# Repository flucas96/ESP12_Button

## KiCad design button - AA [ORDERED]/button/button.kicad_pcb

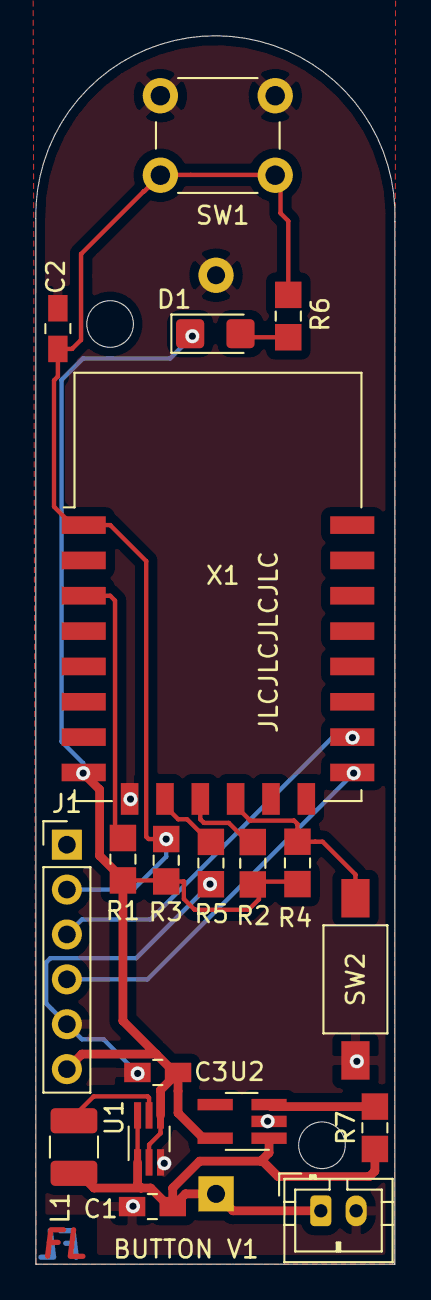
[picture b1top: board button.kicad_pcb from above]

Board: 2 copper layers, 20.3 x 69.5 mm, 20 parts (1 on the bottom side), 13 nets.

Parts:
BT1: Battery_Cell; BatteryHolder_Keystone_2460_1xAA
BT2: Battery_Cell; JST_PH_B2B-PH-K_1x02_P2.00mm_Vertical
C1, C3: 10uF; C_0805_2012handsodermod
C2: 100nF; C_0805_2012handsodermod
D1: LED; LED_1206_3216Metric_Castellated
J1: Conn_01x06_Male; PinHeader_1x06_P2.54mm_Vertical
L1: 4.7 uH; L_1210_3225Metric_Pad1.42x2.65mm_HandSolder
R1, R2, R3, R4, R7: 10k; R_0805_2012handsoldermod
R5: 4.7k; R_0805_2012handsoldermod
R6: 1k; R_0805_2012handsoldermod
SW1: SW_Push; SW_PUSH_6mm
SW2: SW_Push; button_smd_hmsensor
U1: TLV61224; SOT-363_SC-70-6_Handsoldering
U2: AP2112K-3.3; SOT-23-5_HandSolderingmod
X1: ESP-12E

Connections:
/EN: R1.2, X1.3
/GND: BT1.2, BT2.2, C1.1, C2.1, C3.2, J1.5, R5.1, SW1.2, SW2.2, U1.3, U2.2, X1.9
/GPIO0: R4.2, SW2.1, X1.12
/GPIO2: R2.2, X1.11
/GPIO15: R5.2, X1.10
/RST: C2.2, J1.2, R3.2, R6.2, SW1.1, X1.1
/RX: J1.4, X1.15
/TX: J1.3, X1.16
/VCC: C3.1, D1.1, J1.6, R1.1, R2.1, R3.1, R4.1, U1.2, U1.4, U2.5, X1.8
unnamed: BT1.1, BT2.1, C1.2, L1.1, R7.1, U1.1, U1.6, U2.1
unnamed: D1.2, R6.1
unnamed: L1.2, U1.5
unnamed: R7.2, U2.3

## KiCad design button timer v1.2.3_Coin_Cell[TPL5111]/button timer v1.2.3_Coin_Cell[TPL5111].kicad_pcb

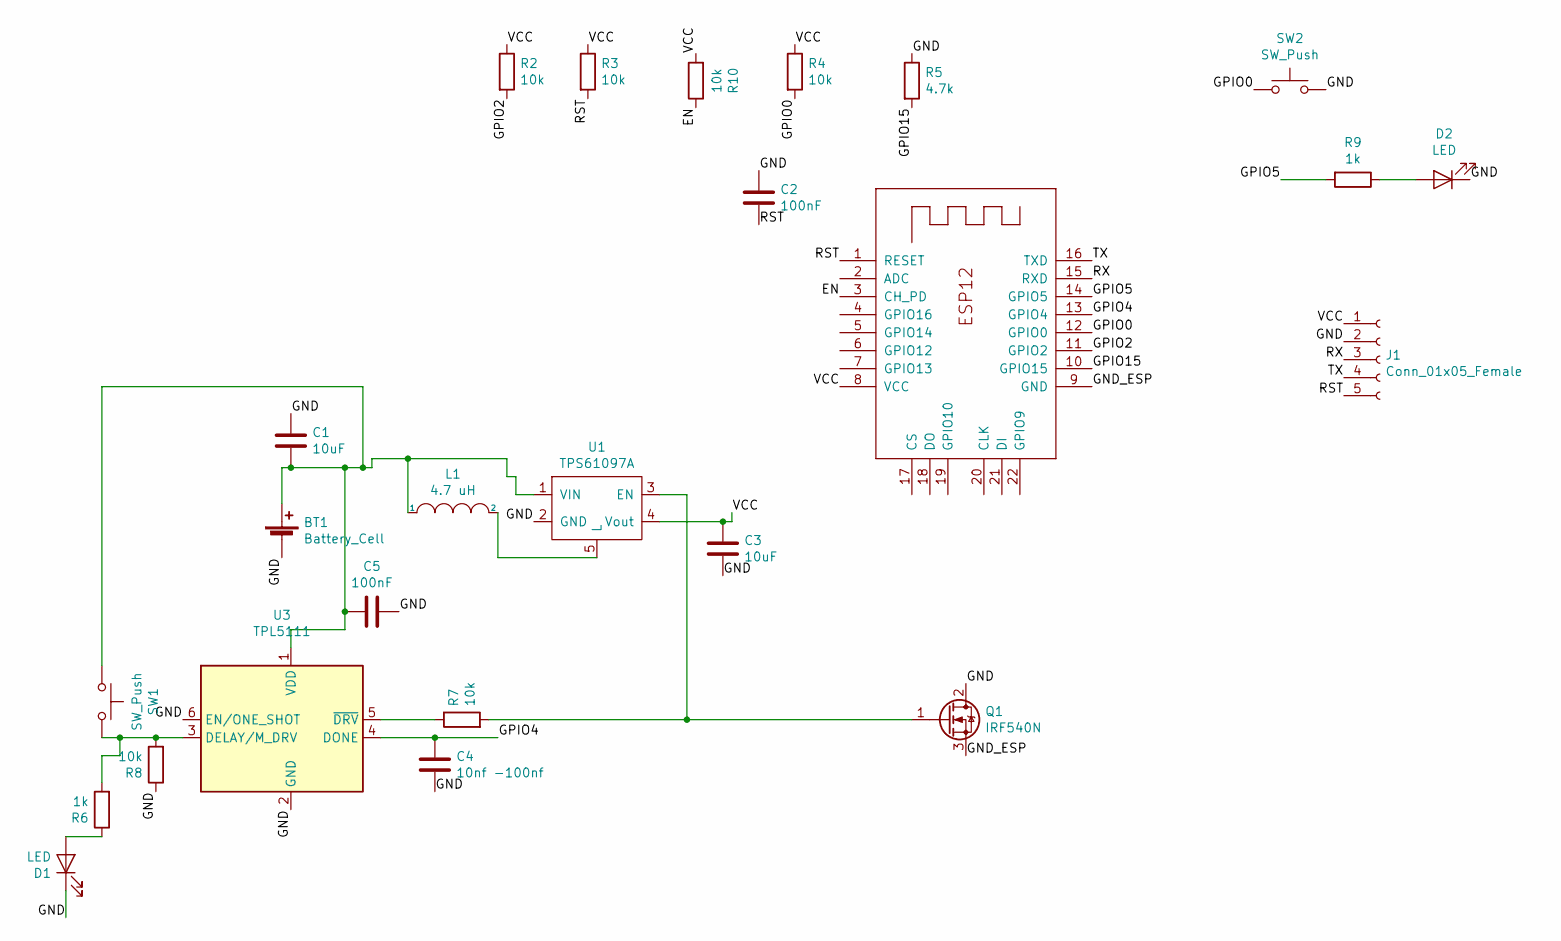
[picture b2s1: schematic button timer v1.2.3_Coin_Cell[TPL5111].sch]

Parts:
BT1: Battery_Cell; BatteryHolder_Keystone_1058_1x2032
C1, C3: 10uF; C_0805_2012handsodermod
C2, C5: 100nF; C_0805_2012handsodermod
C4: 10nf -100nf; C_0402_1005Metric_Pad0.74x0.62mm_HandSoldermod
D1: LED; LED_1206_3216Metric_Castellated
D2: LED; LED_0805_2012Metric_Castellated
J1: Conn_01x05_Female; PinSocket_1x05_P2.54mm_Vertical_mod
L1: 4.7 uH; SMD-1210_Pol_inductor
Q1: IRF540N; SOT-23
R2, R3, R4, R7, R8: 10k; R_0805_2012handsoldermod
R5: 4.7k; R_0805_2012handsoldermod
R6, R9: 1k; R_0805_2012handsoldermod
R10: 10k; R_0603_1608Metric_Pad0.98x0.95mm_HandSolder
SW1: SW_Push; SW_PUSH_6mm_H8mm_mod
SW2: SW_Push; SW_SPST_B3U-1000P_mod
U1: TPS61097A; SOT-23-5_HandSolderingmod
U3: TPL5111; SOT-23-6handsoldering
X1: ESP-12E; ESP-12Elesssilk

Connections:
/EN: R10.1, X1.3 (CH_PD)
/GND: BT1.2 (-), C1.1, C2.1, C3.2, C4.2, C5.1, D1.1 (K), D2.1 (K), J1.2, Q1.2 (D), R5.1, R8.1, SW2.2, U1.2 (GND), U3.2 (GND), U3.6 (EN/ONE_SHOT)
/GND_ESP: Q1.3 (S), X1.9 (GND)
/GPIO0: R4.2, SW2.1, X1.12 (GPIO0)
/GPIO2: R2.2, X1.11 (GPIO2)
/GPIO4: C4.1, U3.4 (DONE), X1.13 (GPIO4)
/GPIO5: R9.2, X1.14 (GPIO5)
/GPIO15: R5.2, X1.10 (GPIO15)
/RST: C2.2, J1.5, R3.2, X1.1 (RESET)
/RX: J1.3, X1.15 (RXD)
/TX: J1.4, X1.16 (TXD)
/VCC: C3.1, J1.1, R2.1, R3.1, R4.1, R10.2, U1.4 (Vout), X1.8 (VCC)
unnamed: BT1.1 (+), C1.2, C5.2, L1.1, SW1.1, U1.1 (VIN), U3.1 (VDD)
unnamed: D1.2 (A), R6.1
unnamed: D2.2 (A), R9.1
unnamed: L1.2, U1.5 (L)
unnamed: Q1.1 (G), R7.2, U1.3 (EN)
unnamed: R6.2, R8.2, SW1.2, U3.3 (DELAY/M_DRV)
unnamed: R7.1, U3.5 (~DRV)

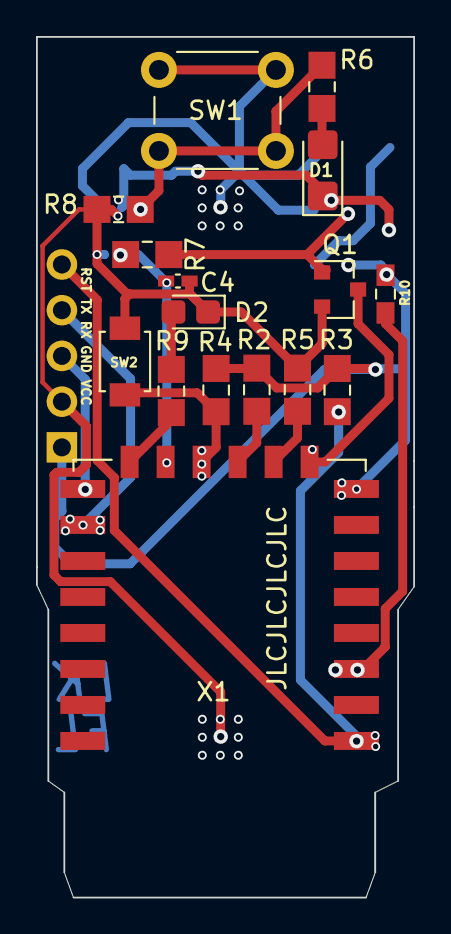
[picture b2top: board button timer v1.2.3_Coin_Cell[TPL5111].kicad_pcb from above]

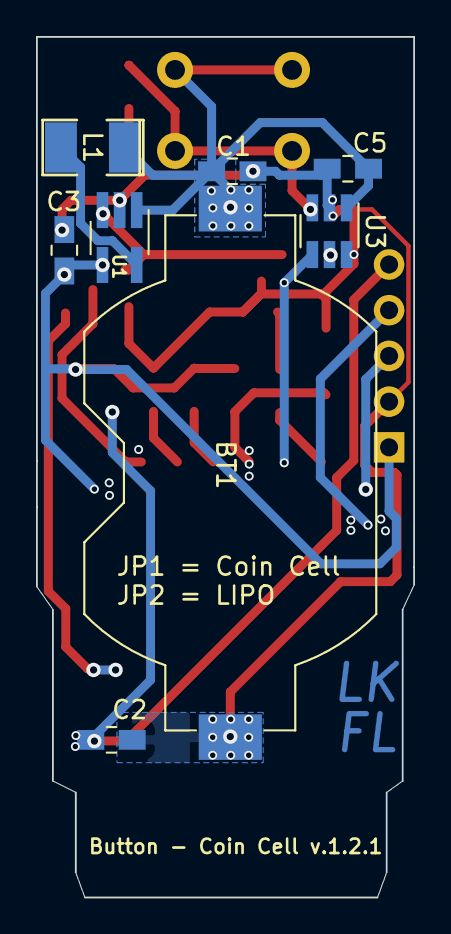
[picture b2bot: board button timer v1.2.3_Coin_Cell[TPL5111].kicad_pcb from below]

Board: 2 copper layers, 21.0 x 47.8 mm, 25 parts (8 on the bottom side), 19 nets.
